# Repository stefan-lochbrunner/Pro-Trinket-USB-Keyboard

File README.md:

Pro-Trinket-USB-Keyboard
========================
A small device for programmable keyboard shortcuts.
For more infos please see [**HaD.io project page**](https://hackaday.io/project/3502-pro-trinket-usb-keyboard)

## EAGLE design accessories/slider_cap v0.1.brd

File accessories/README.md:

Accessories for the Pro Trinket Keyboard v4.2 and up

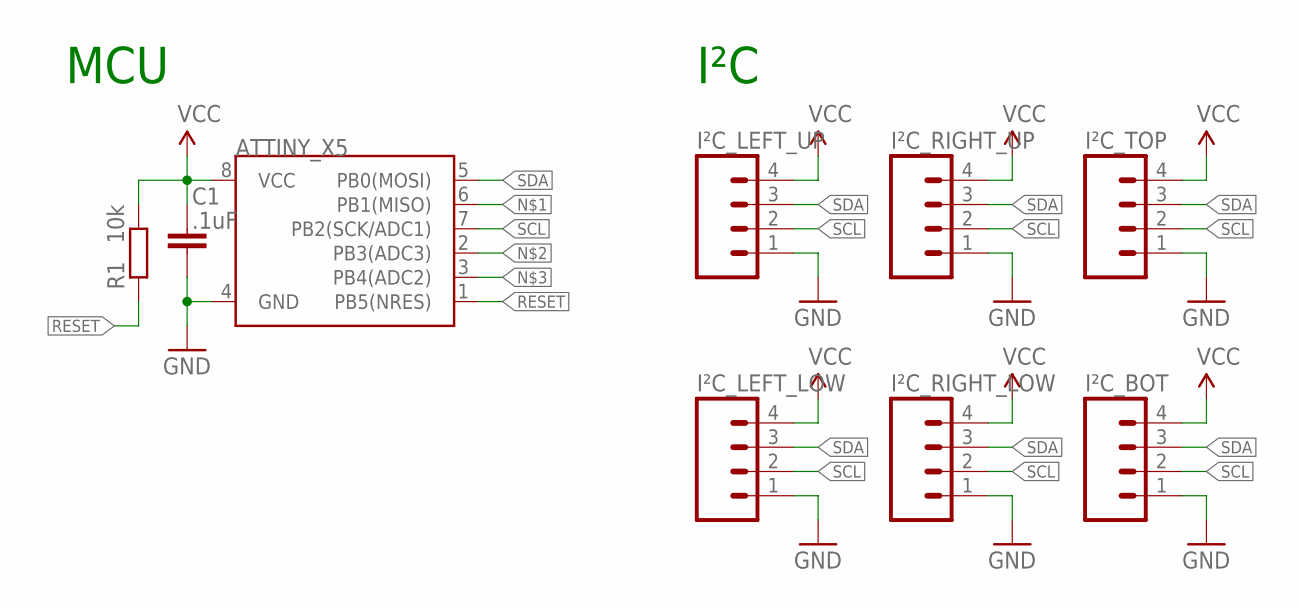
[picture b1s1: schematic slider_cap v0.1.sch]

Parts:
ATTINY_X5: ATTINY45TINY45-20-SMT; SO08-EIAJ
C1: .1uF; C805
I²C_BOT: M04PTH; 1X04
I²C_LEFT_LOW: M04PTH; 1X04
I²C_LEFT_UP: M04PTH; 1X04
I²C_RIGHT_LOW: M04PTH; 1X04
I²C_RIGHT_UP: M04PTH; 1X04
I²C_TOP: M04PTH; 1X04
R1: 10k; R805

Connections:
GND: ATTINY_X5.4 (GND), C1.2, I²C_BOT.1, I²C_LEFT_LOW.1, I²C_LEFT_UP.1, I²C_RIGHT_LOW.1, I²C_RIGHT_UP.1, I²C_TOP.1
RESET: ATTINY_X5.1 (PB5(NRES)), R1.1
SCL: ATTINY_X5.7 (PB2(SCK/ADC1)), I²C_BOT.2, I²C_LEFT_LOW.2, I²C_LEFT_UP.2, I²C_RIGHT_LOW.2, I²C_RIGHT_UP.2, I²C_TOP.2
SDA: ATTINY_X5.5 (PB0(MOSI)), I²C_BOT.3, I²C_LEFT_LOW.3, I²C_LEFT_UP.3, I²C_RIGHT_LOW.3, I²C_RIGHT_UP.3, I²C_TOP.3
VCC: ATTINY_X5.8 (VCC), C1.1, I²C_BOT.4, I²C_LEFT_LOW.4, I²C_LEFT_UP.4, I²C_RIGHT_LOW.4, I²C_RIGHT_UP.4, I²C_TOP.4, R1.2

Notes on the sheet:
I²C
MCU

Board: 2 copper layers, 9 parts (3 on the bottom side), 5 nets, no tracks yet.

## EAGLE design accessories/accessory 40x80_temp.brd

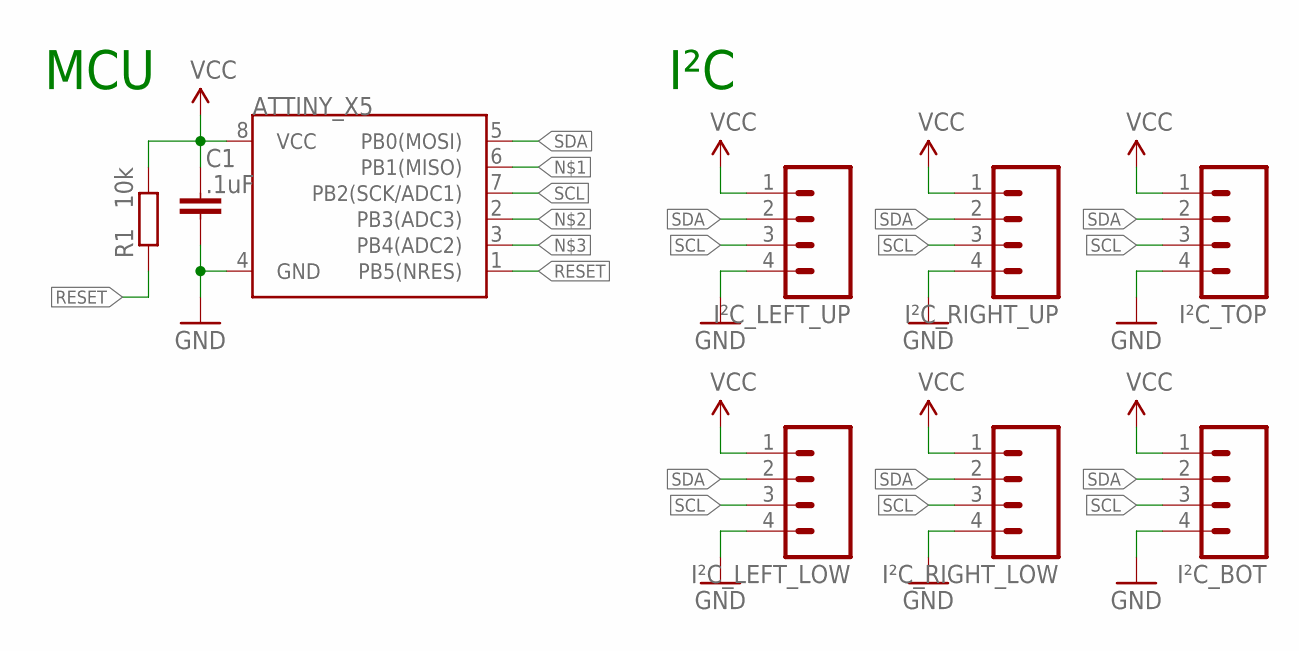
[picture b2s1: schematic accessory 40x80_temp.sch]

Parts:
ATTINY_X5: ATTINY45TINY45-20-SMT; SO08-EIAJ
C1: .1uF; C805
I²C_BOT: M04PTH; 1X04
I²C_LEFT_LOW: M04PTH; 1X04
I²C_LEFT_UP: M04PTH; 1X04
I²C_RIGHT_LOW: M04PTH; 1X04
I²C_RIGHT_UP: M04PTH; 1X04
I²C_TOP: M04PTH; 1X04
R1: 10k; R805

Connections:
GND: ATTINY_X5.4 (GND), C1.2, I²C_BOT.4, I²C_LEFT_LOW.4, I²C_LEFT_UP.4, I²C_RIGHT_LOW.4, I²C_RIGHT_UP.4, I²C_TOP.4
RESET: ATTINY_X5.1 (PB5(NRES)), R1.1
SCL: ATTINY_X5.7 (PB2(SCK/ADC1)), I²C_BOT.3, I²C_LEFT_LOW.3, I²C_LEFT_UP.3, I²C_RIGHT_LOW.3, I²C_RIGHT_UP.3, I²C_TOP.3
SDA: ATTINY_X5.5 (PB0(MOSI)), I²C_BOT.2, I²C_LEFT_LOW.2, I²C_LEFT_UP.2, I²C_RIGHT_LOW.2, I²C_RIGHT_UP.2, I²C_TOP.2
VCC: ATTINY_X5.8 (VCC), C1.1, I²C_BOT.1, I²C_LEFT_LOW.1, I²C_LEFT_UP.1, I²C_RIGHT_LOW.1, I²C_RIGHT_UP.1, I²C_TOP.1, R1.2

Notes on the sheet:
I²C
MCU

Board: 2 copper layers, 9 parts (3 on the bottom side), 5 nets, no tracks yet.

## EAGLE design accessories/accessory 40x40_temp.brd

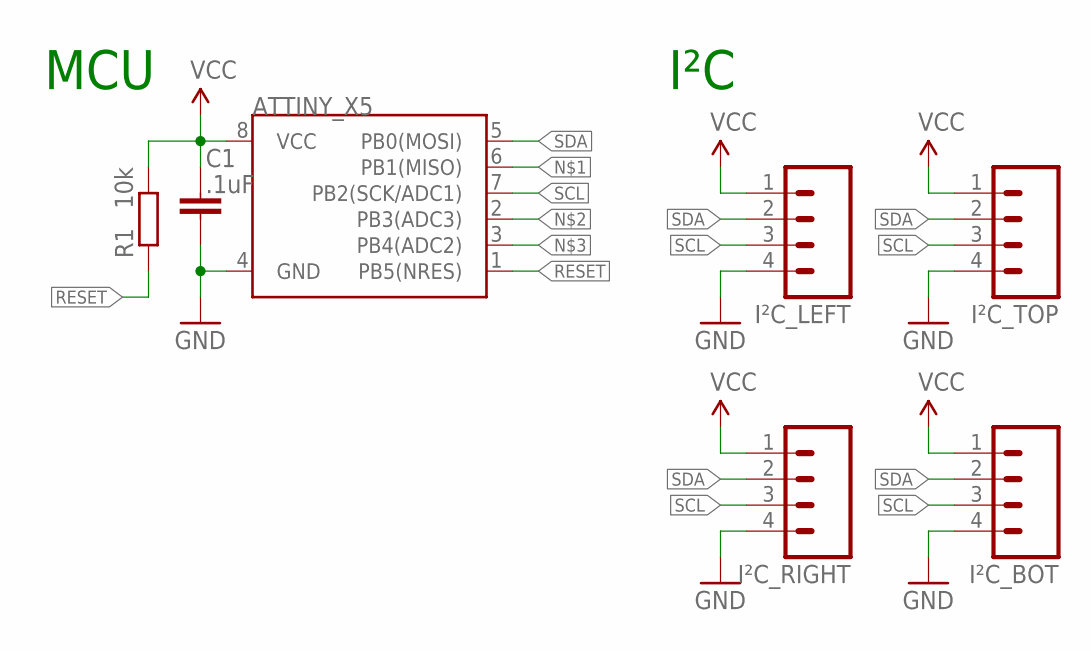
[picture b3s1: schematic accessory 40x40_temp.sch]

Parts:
ATTINY_X5: ATTINY45TINY45-20-SMT; SO08-EIAJ
C1: .1uF; C805
I²C_BOT: M04PTH; 1X04
I²C_LEFT: M04PTH; 1X04
I²C_RIGHT: M04PTH; 1X04
I²C_TOP: M04PTH; 1X04
R1: 10k; R805

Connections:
GND: ATTINY_X5.4 (GND), C1.2, I²C_BOT.4, I²C_LEFT.4, I²C_RIGHT.4, I²C_TOP.4
RESET: ATTINY_X5.1 (PB5(NRES)), R1.1
SCL: ATTINY_X5.7 (PB2(SCK/ADC1)), I²C_BOT.3, I²C_LEFT.3, I²C_RIGHT.3, I²C_TOP.3
SDA: ATTINY_X5.5 (PB0(MOSI)), I²C_BOT.2, I²C_LEFT.2, I²C_RIGHT.2, I²C_TOP.2
VCC: ATTINY_X5.8 (VCC), C1.1, I²C_BOT.1, I²C_LEFT.1, I²C_RIGHT.1, I²C_TOP.1, R1.2

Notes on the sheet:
I²C
MCU

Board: 2 copper layers, 7 parts (3 on the bottom side), 5 nets, no tracks yet.

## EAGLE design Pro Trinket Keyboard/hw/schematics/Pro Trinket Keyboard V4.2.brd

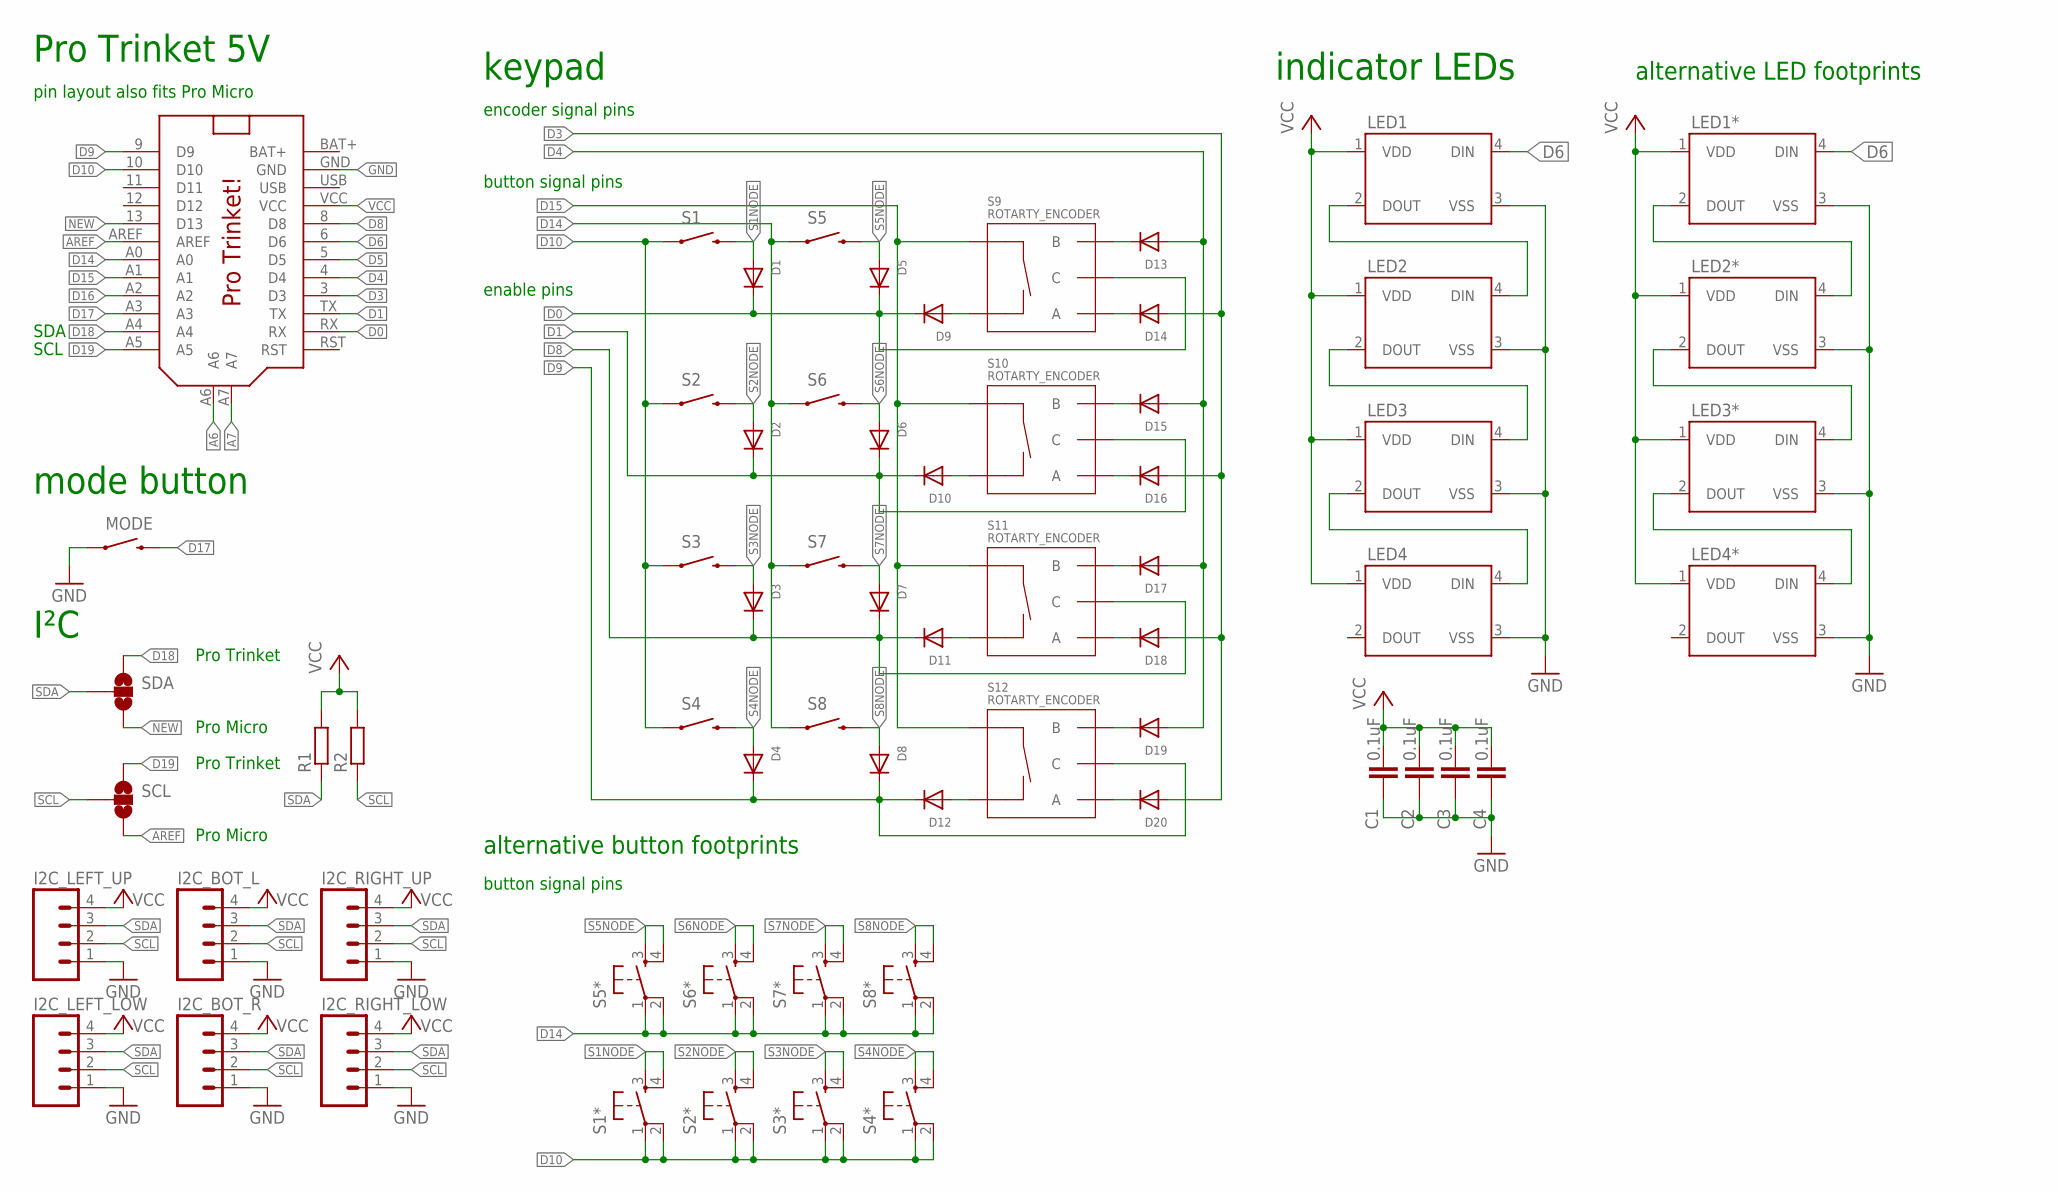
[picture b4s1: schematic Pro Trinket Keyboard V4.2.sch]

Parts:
C1, C2, C3, C4: 0.1uF; 0603-CAP
D1, D2, D3, D4, D5, D6, D7, D8, D9, D10, D11, D12, D13, D14, D15, D16, D17, D18, D19, D20: DIODESOD-123; SOD-123
I2C_BOT_L, I2C_BOT_R, I2C_LEFT_LOW, I2C_LEFT_UP, I2C_RIGHT_LOW, I2C_RIGHT_UP: M04PTH; 1X04
LED1, LED1*, LED2, LED2*, LED3, LED3*, LED4, LED4*: WS2812B
MODE: SWITCH-MOMENTARY-2SIDE_EZ; TACTILE-PTH-SIDEEZ
PRO_TRINKET: PRO_TRINKET; PROTRINKET
R1, R2: RESISTORR805-0805; R805
S1, S2, S3, S4, S5, S6, S7, S8: SWITCH-MOMENTARY-212MM; TACTILE-PTH-12MM
S1*, S2*, S3*, S4*, S5*, S6*, S7*, S8*: TACTILE-SWITCH-PTH; TAC-SWITCH-PTH
S9, S10, S11, S12: ROTARTY_ENCODER; ROTARY_ENC_PLAIN
SCL: SOLDERJUMPER_2WAYS; SJ_3
SDA: SOLDERJUMPER_2WAYS; SJ_3

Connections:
A6: PRO_TRINKET.A6
A7: PRO_TRINKET.A7
AREF: PRO_TRINKET.AREF, SCL.3
BAT+: PRO_TRINKET.BAT+
D0: D1.C, D5.C, D9.C, PRO_TRINKET.RX, S9.C
D1: D2.C, D6.C, D10.C, PRO_TRINKET.TX, S10.C
D3: D14.A, D16.A, D18.A, D20.A, PRO_TRINKET.3 (D3)
D4: D13.A, D15.A, D17.A, D19.A, PRO_TRINKET.4 (D4)
D5: PRO_TRINKET.5 (D5)
D6: LED1.4 (DIN), LED1*.4 (DIN), PRO_TRINKET.6 (D6)
D8: D3.C, D7.C, D11.C, PRO_TRINKET.8 (D8), S11.C
D9: D4.C, D8.C, D12.C, PRO_TRINKET.9 (D9), S12.C
D10: PRO_TRINKET.10 (D10), S1.1, S1.2 (1), S1*.1, S1*.2, S2.1, S2.2 (1), S2*.1, S2*.2, S3.1, S3.2 (1), S3*.1, S3*.2, S4.1, S4.2 (1), S4*.1, S4*.2
D14: PRO_TRINKET.A0, S5.1, S5.2 (1), S5*.1, S5*.2, S6.1, S6.2 (1), S6*.1, S6*.2, S7.1, S7.2 (1), S7*.1, S7*.2, S8.1, S8.2 (1), S8*.1, S8*.2
D15: PRO_TRINKET.A1, S9.SW+, S10.SW+, S11.SW+, S12.SW+
D16: PRO_TRINKET.A2
D17: MODE.2, PRO_TRINKET.A3
D18: PRO_TRINKET.A4, SDA.1
D19: PRO_TRINKET.A5, SCL.1
GND: C1.1, C2.1, C3.1, C4.1, I2C_BOT_L.1, I2C_BOT_R.1, I2C_LEFT_LOW.1, I2C_LEFT_UP.1, I2C_RIGHT_LOW.1, I2C_RIGHT_UP.1, LED1.3 (VSS), LED1*.3 (VSS), LED2.3 (VSS), LED2*.3 (VSS), LED3.3 (VSS), LED3*.3 (VSS), LED4.3 (VSS), LED4*.3 (VSS), MODE.1, PRO_TRINKET.GND
L1NODE: LED1.2 (DOUT), LED1*.2 (DOUT), LED2.4 (DIN), LED2*.4 (DIN)
L2NODE: LED2.2 (DOUT), LED2*.2 (DOUT), LED3.4 (DIN), LED3*.4 (DIN)
L3NODE: LED3.2 (DOUT), LED3*.2 (DOUT), LED4.4 (DIN), LED4*.4 (DIN)
unnamed: D10.A, S10.SW-
unnamed: D9.A, S9.SW-
unnamed: D11.A, S11.SW-
unnamed: D20.C, S12.A
unnamed: D19.C, S12.B
unnamed: D18.C, S11.A
unnamed: D12.A, S12.SW-
unnamed: D16.C, S10.A
unnamed: D15.C, S10.B
unnamed: D14.C, S9.A
unnamed: D13.C, S9.B
unnamed: D17.C, S11.B
NEW: PRO_TRINKET.13 (D13), SDA.3
S1NODE: D1.A, S1.3 (2), S1.4 (2), S1*.3, S1*.4
S2NODE: D2.A, S2.3 (2), S2.4 (2), S2*.3, S2*.4
S3NODE: D3.A, S3.3 (2), S3.4 (2), S3*.3, S3*.4
S4NODE: D4.A, S4.3 (2), S4.4 (2), S4*.3, S4*.4
S5NODE: D5.A, S5.3 (2), S5.4 (2), S5*.3, S5*.4
S6NODE: D6.A, S6.3 (2), S6.4 (2), S6*.3, S6*.4
S7NODE: D7.A, S7.3 (2), S7.4 (2), S7*.3, S7*.4
S8NODE: D8.A, S8.3 (2), S8.4 (2), S8*.3, S8*.4
SCL: I2C_BOT_L.2, I2C_BOT_R.2, I2C_LEFT_LOW.2, I2C_LEFT_UP.2, I2C_RIGHT_LOW.2, I2C_RIGHT_UP.2, R2.1, SCL.2
SDA: I2C_BOT_L.3, I2C_BOT_R.3, I2C_LEFT_LOW.3, I2C_LEFT_UP.3, I2C_RIGHT_LOW.3, I2C_RIGHT_UP.3, R1.1, SDA.2
USB: PRO_TRINKET.USB
VCC: C1.2, C2.2, C3.2, C4.2, I2C_BOT_L.4, I2C_BOT_R.4, I2C_LEFT_LOW.4, I2C_LEFT_UP.4, I2C_RIGHT_LOW.4, I2C_RIGHT_UP.4, LED1.1 (VDD), LED1*.1 (VDD), LED2.1 (VDD), LED2*.1 (VDD), LED3.1 (VDD), LED3*.1 (VDD), LED4.1 (VDD), LED4*.1 (VDD), PRO_TRINKET.VCC, R1.2, R2.2

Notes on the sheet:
keypad
mode button
indicator LEDs
Pro Trinket 5V
enable pins
encoder signal pins
button signal pins
alternative button footprints
alternative LED footprints
pin layout also fits Pro Micro
I²C
SDA
SCL
Pro Trinket
Pro Micro

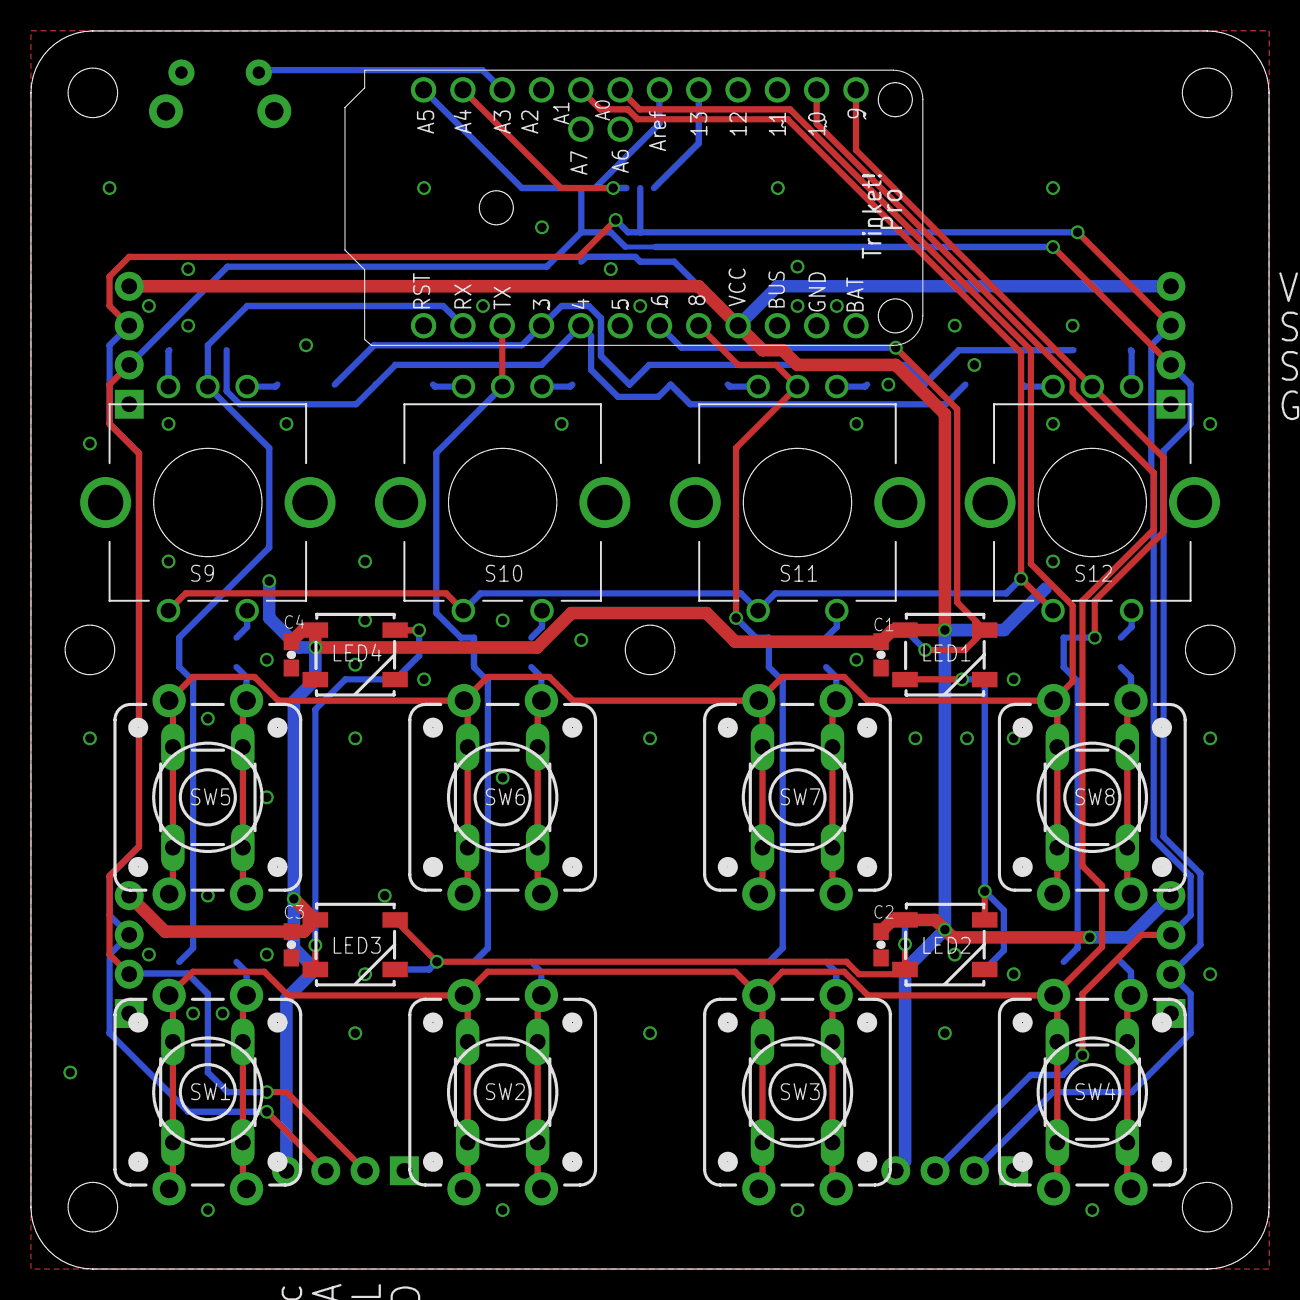
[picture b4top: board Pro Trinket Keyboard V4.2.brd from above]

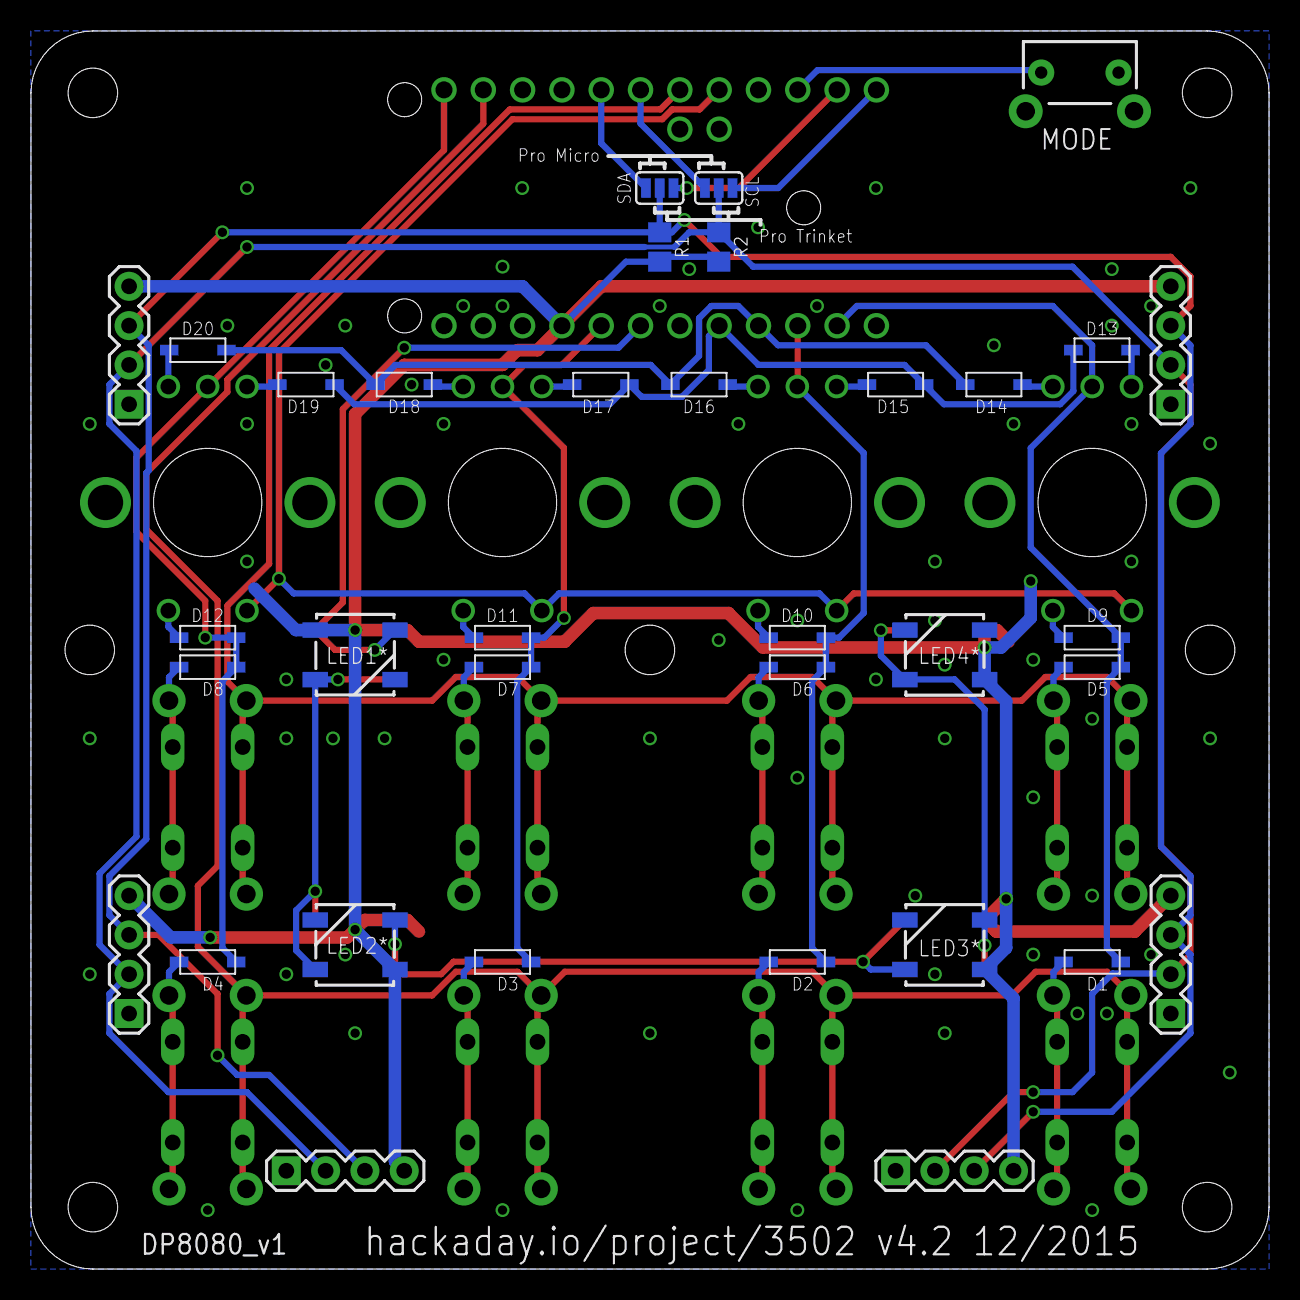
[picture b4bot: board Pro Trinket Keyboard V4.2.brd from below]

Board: 2 copper layers, 80.0 x 80.0 mm, 65 parts (35 on the bottom side), 42 nets.

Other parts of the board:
U$1: DP8080_V1

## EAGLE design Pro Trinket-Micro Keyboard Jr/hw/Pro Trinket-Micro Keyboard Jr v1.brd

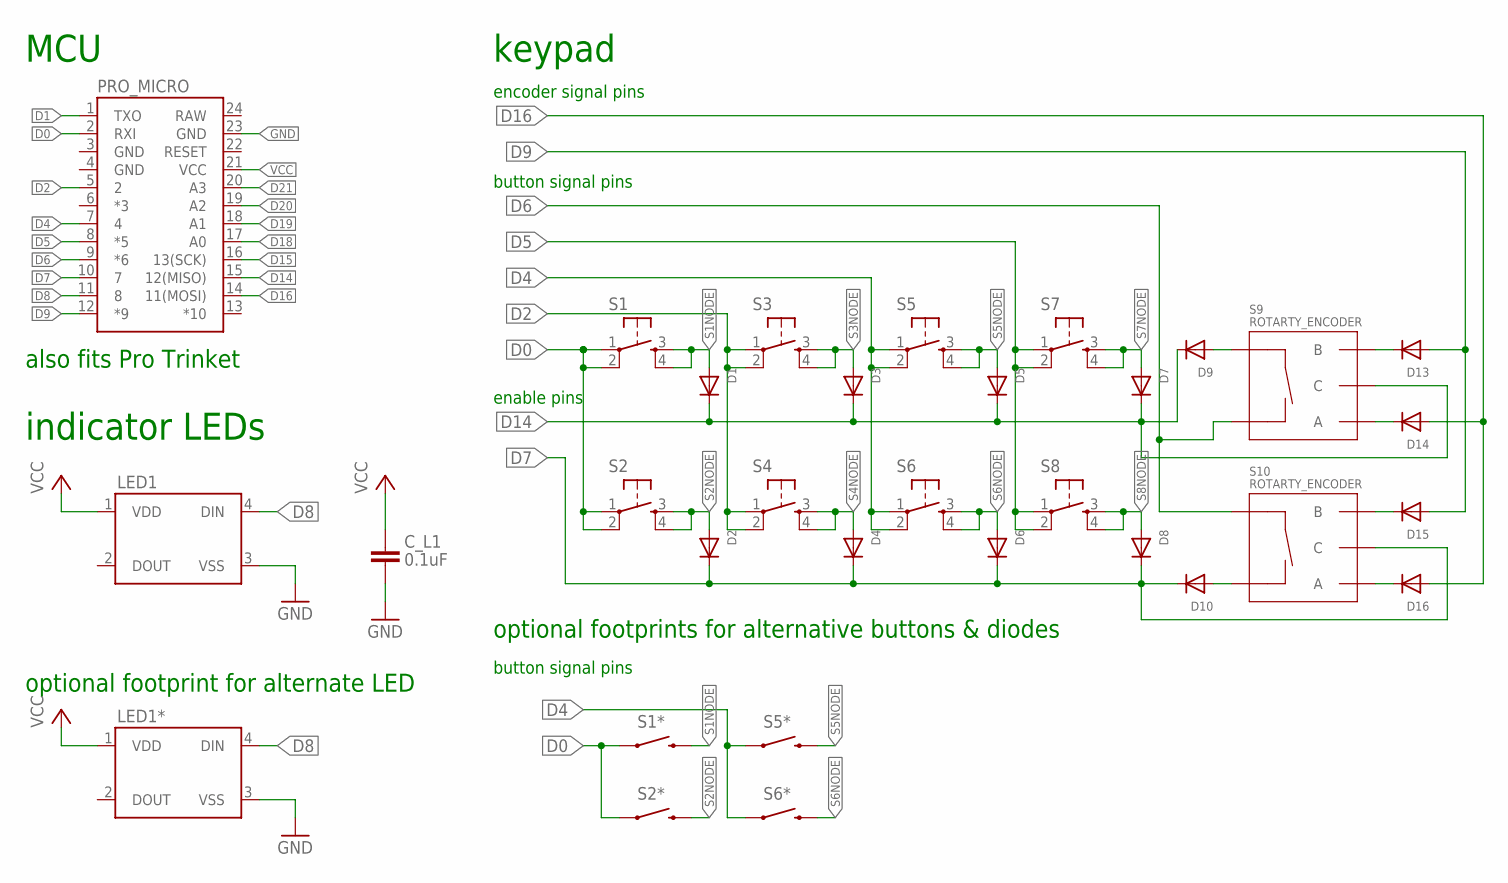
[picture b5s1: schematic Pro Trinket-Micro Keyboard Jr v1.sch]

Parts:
C_L1: 0.1uF; 0603-CAP
D1, D2, D3, D4, D5, D6, D7, D8, D9, D10, D13, D14, D15, D16: DIODESOD-123; SOD-123
LED1, LED1*: WS2812B
PRO_MICRO: ARDUINO_PRO_MICRO
S1, S2, S3, S4, S5, S6, S7, S8: TACTILE-SWITCH-PTH; TAC-SWITCH-PTH
S1*, S2*, S5*, S6*: SWITCH-MOMENTARY-212MM; TACTILE-PTH-12MM
S9, S10: ROTARTY_ENCODER; ROTARY_ENC_PLAIN

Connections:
D0: PRO_MICRO.2 (RXI), S1.1, S1.2, S1*.1, S1*.2 (1), S2.1, S2.2, S2*.1, S2*.2 (1)
D1: PRO_MICRO.1 (TXO)
D2: PRO_MICRO.5 (2), S3.1, S3.2, S4.1, S4.2
D4: PRO_MICRO.7 (4), S5.1, S5.2, S5*.1, S5*.2 (1), S6.1, S6.2, S6*.1, S6*.2 (1)
D5: PRO_MICRO.8 (*5), S7.1, S7.2, S8.1, S8.2
D6: PRO_MICRO.9 (*6), S9.SW-, S10.SW+
D7: D2.C, D4.C, D6.C, D8.C, D10.C, PRO_MICRO.10 (7), S10.C
D8: LED1.4 (DIN), LED1*.4 (DIN), PRO_MICRO.11 (8)
D9: D13.A, D15.A, PRO_MICRO.12 (*9)
D14: D1.C, D3.C, D5.C, D7.C, D9.C, PRO_MICRO.15 (12(MISO)), S9.C
D15: PRO_MICRO.16 (13(SCK))
D16: D14.A, D16.A, PRO_MICRO.14 (11(MOSI))
D18: PRO_MICRO.17 (A0)
D19: PRO_MICRO.18 (A1)
D20: PRO_MICRO.19 (A2)
D21: PRO_MICRO.20 (A3)
GND: C_L1.1, LED1.3 (VSS), LED1*.3 (VSS), PRO_MICRO.23 (GND)
unnamed: D9.A, S9.SW+
unnamed: D10.A, S10.SW-
unnamed: D16.C, S10.A
unnamed: D15.C, S10.B
unnamed: D14.C, S9.A
unnamed: D13.C, S9.B
S1NODE: D1.A, S1.3, S1.4, S1*.3 (2), S1*.4 (2)
S2NODE: D2.A, S2.3, S2.4, S2*.3 (2), S2*.4 (2)
S3NODE: D3.A, S3.3, S3.4
S4NODE: D4.A, S4.3, S4.4
S5NODE: D5.A, S5.3, S5.4, S5*.3 (2), S5*.4 (2)
S6NODE: D6.A, S6.3, S6.4, S6*.3 (2), S6*.4 (2)
S7NODE: D7.A, S7.3, S7.4
S8NODE: D8.A, S8.3, S8.4
VCC: C_L1.2, LED1.1 (VDD), LED1*.1 (VDD), PRO_MICRO.21 (VCC)

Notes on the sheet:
keypad
indicator LEDs
enable pins
encoder signal pins
button signal pins
optional footprints for alternative buttons & diodes
optional footprint for alternate LED
MCU
also fits Pro Trinket

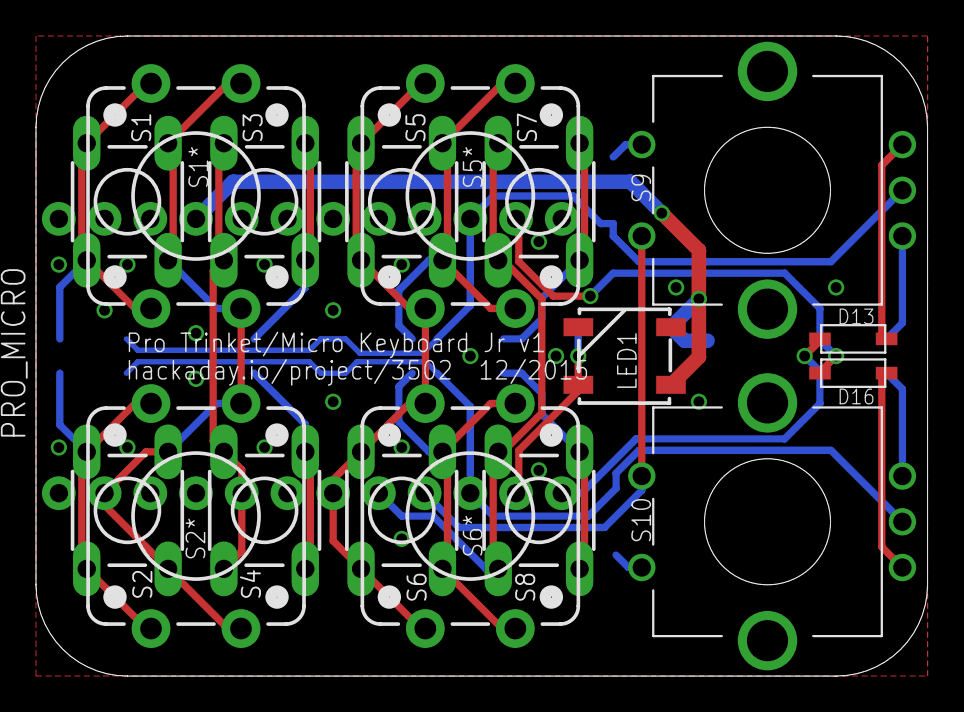
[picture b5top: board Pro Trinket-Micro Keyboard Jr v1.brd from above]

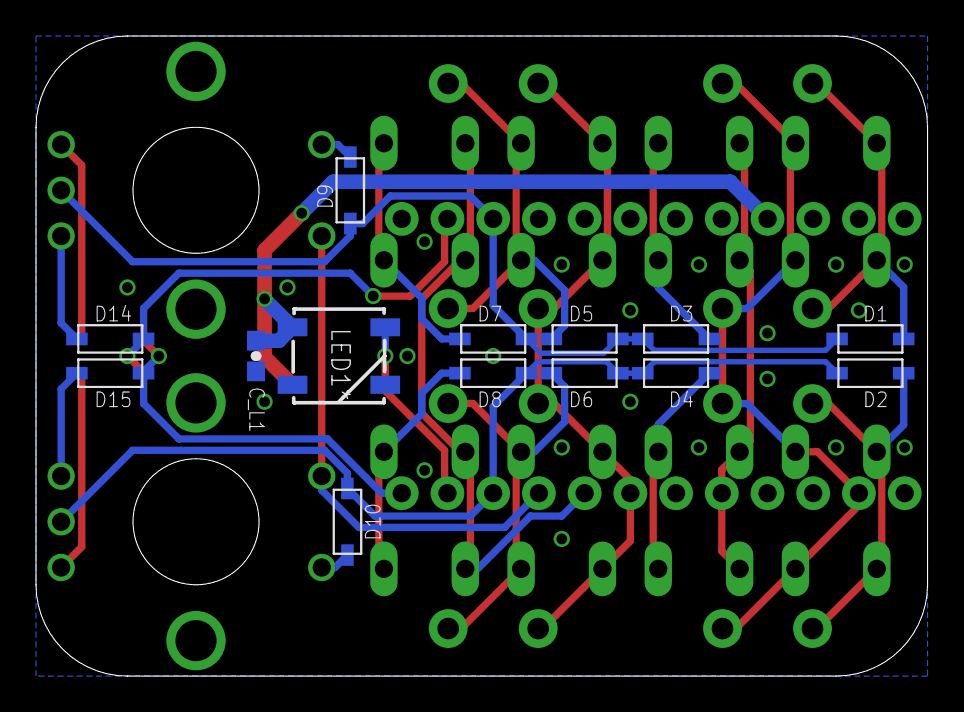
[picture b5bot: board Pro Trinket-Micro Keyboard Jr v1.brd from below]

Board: 2 copper layers, 49.5 x 35.6 mm, 32 parts (14 on the bottom side), 26 nets.

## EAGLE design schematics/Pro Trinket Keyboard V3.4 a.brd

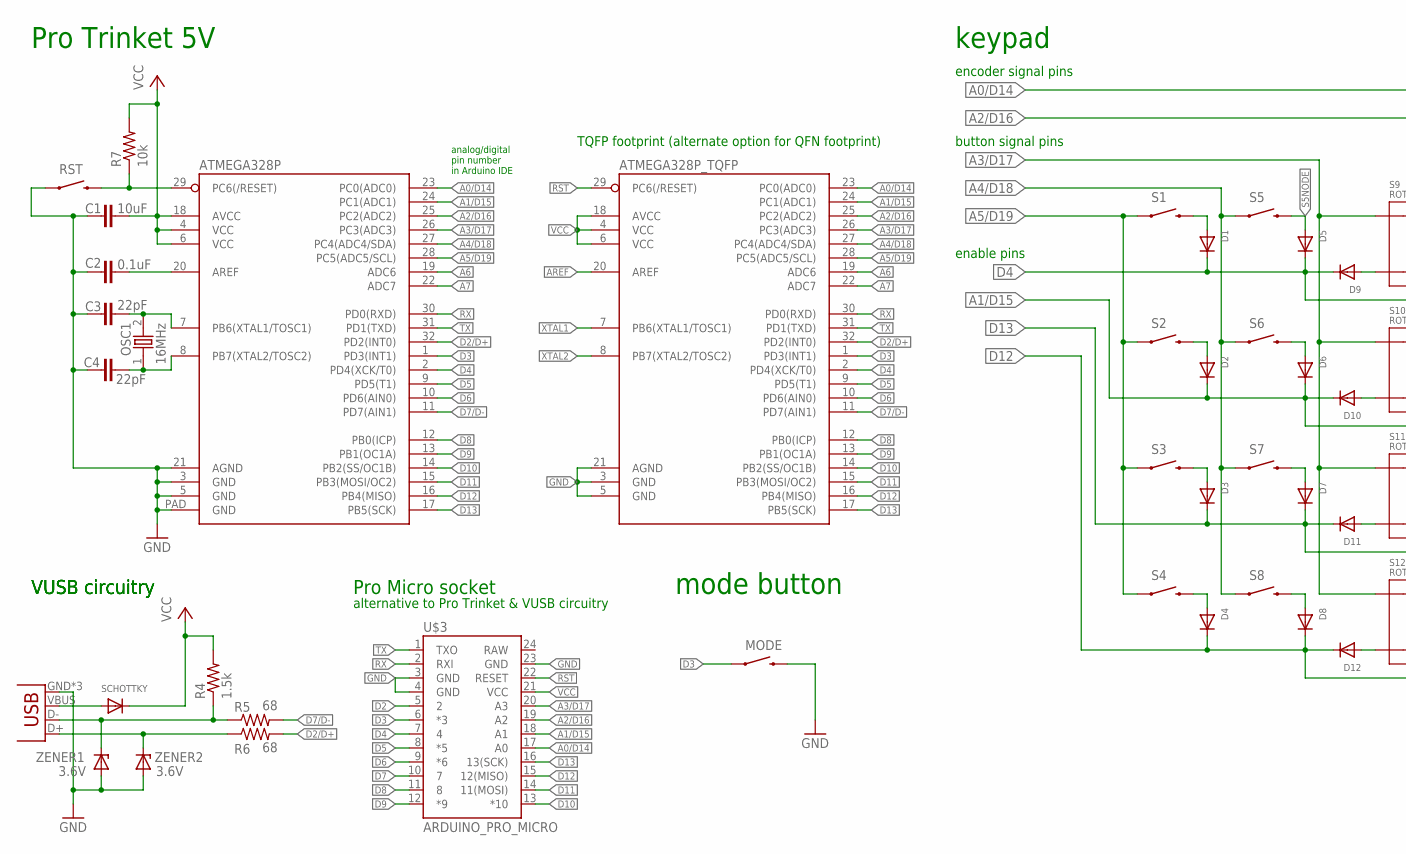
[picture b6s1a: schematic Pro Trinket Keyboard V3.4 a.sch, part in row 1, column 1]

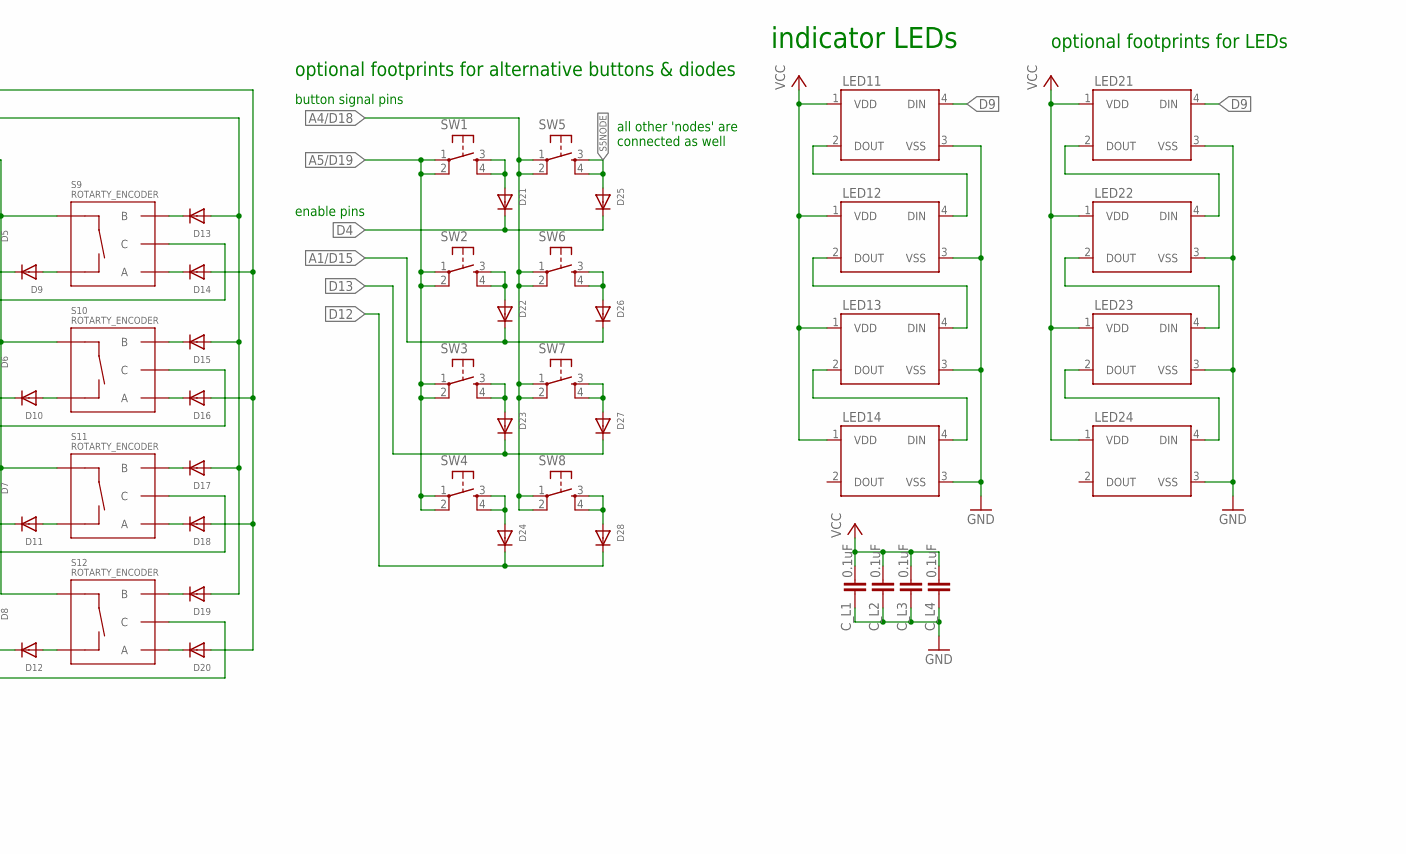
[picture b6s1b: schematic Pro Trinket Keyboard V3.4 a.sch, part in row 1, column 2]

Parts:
ATMEGA328P: ATMEGA328P_MLFMLF32; MLF32-PAD
ATMEGA328P_TQFP: ATMEGA328P_TQFP; TQFP32-08
C1: 10uF; 0603-CAP
C2: 0.1uF; 0603-CAP
C3, C4: 22pF; 0603-CAP
C_L1, C_L2, C_L3, C_L4: 0.1uF; 0603-CAP
D1, D2, D3, D4, D5, D6, D7, D8, D9, D10, D11, D12, D13, D14, D15, D16, D17, D18, D19, D20, D21, D22, D23, D24, D25, D26, D27, D28: DIODESOD-123; SOD-123
LED11, LED12, LED13, LED14, LED21, LED22, LED23, LED24: WS2812B
MODE: SWITCH-MOMENTARY-2SIDE_EZ; TACTILE-PTH-SIDEEZ
OSC1: 16MHz; HC-49U
R4: 1.5k; 0805
R5, R6: 68; 0805
R7: 10k; 0805
RST: SWITCH-MOMENTARY-2SIDE_EZ; TACTILE-PTH-SIDEEZ
S1, S2, S3, S4, S5, S6, S7, S8: SWITCH-MOMENTARY-212MM; TACTILE-PTH-12MM
S9, S10, S11, S12: ROTARTY_ENCODER; ROTARY_ENC_PLAIN
SCHOTTKY: DIODESMA; SMADIODE
SW1, SW2, SW3, SW4, SW5, SW6, SW7, SW8: TACTILE-SWITCH-PTH; TAC-SWITCH-PTH
U$3: ARDUINO_PRO_MICRO
UUSB: USB-MICROB
ZENER1, ZENER2: 3.6V; SOD80C

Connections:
A0/D14: ATMEGA328P.23 (PC0(ADC0)), ATMEGA328P_TQFP.23 (PC0(ADC0)), D14.A, D16.A, D18.A, D20.A, U$3.17 (A0)
A1/D15: ATMEGA328P.24 (PC1(ADC1)), ATMEGA328P_TQFP.24 (PC1(ADC1)), D2.C, D6.C, D10.C, D22.C, D26.C, S10.C, U$3.18 (A1)
A2/D16: ATMEGA328P.25 (PC2(ADC2)), ATMEGA328P_TQFP.25 (PC2(ADC2)), D13.A, D15.A, D17.A, D19.A, U$3.19 (A2)
A3/D17: ATMEGA328P.26 (PC3(ADC3)), ATMEGA328P_TQFP.26 (PC3(ADC3)), S9.SW+, S10.SW+, S11.SW+, S12.SW+, U$3.20 (A3)
A4/D18: ATMEGA328P.27 (PC4(ADC4/SDA)), ATMEGA328P_TQFP.27 (PC4(ADC4/SDA)), S5.1, S5.2 (1), S6.1, S6.2 (1), S7.1, S7.2 (1), S8.1, S8.2 (1), SW5.1, SW5.2, SW6.1, SW6.2, SW7.1, SW7.2, SW8.1, SW8.2
A5/D19: ATMEGA328P.28 (PC5(ADC5/SCL)), ATMEGA328P_TQFP.28 (PC5(ADC5/SCL)), S1.1, S1.2 (1), S2.1, S2.2 (1), S3.1, S3.2 (1), S4.1, S4.2 (1), SW1.1, SW1.2, SW2.1, SW2.2, SW3.1, SW3.2, SW4.1, SW4.2
A6: ATMEGA328P.19 (ADC6), ATMEGA328P_TQFP.19 (ADC6)
A7: ATMEGA328P.22 (ADC7), ATMEGA328P_TQFP.22 (ADC7)
AREF: ATMEGA328P.20 (AREF), ATMEGA328P_TQFP.20 (AREF), C2.2
D2: U$3.5 (2)
D2/D+: ATMEGA328P.32 (PD2(INT0)), ATMEGA328P_TQFP.32 (PD2(INT0)), R6.2
D3: ATMEGA328P.1 (PD3(INT1)), ATMEGA328P_TQFP.1 (PD3(INT1)), MODE.1, U$3.6 (*3)
D4: ATMEGA328P.2 (PD4(XCK/T0)), ATMEGA328P_TQFP.2 (PD4(XCK/T0)), D1.C, D5.C, D9.C, D21.C, D25.C, S9.C, U$3.7 (4)
D5: ATMEGA328P.9 (PD5(T1)), ATMEGA328P_TQFP.9 (PD5(T1)), U$3.8 (*5)
D6: ATMEGA328P.10 (PD6(AIN0)), ATMEGA328P_TQFP.10 (PD6(AIN0)), U$3.9 (*6)
D7: U$3.10 (7)
D7/D-: ATMEGA328P.11 (PD7(AIN1)), ATMEGA328P_TQFP.11 (PD7(AIN1)), R5.2
D8: ATMEGA328P.12 (PB0(ICP)), ATMEGA328P_TQFP.12 (PB0(ICP)), U$3.11 (8)
D9: ATMEGA328P.13 (PB1(OC1A)), ATMEGA328P_TQFP.13 (PB1(OC1A)), LED11.4 (DIN), LED21.4 (DIN), U$3.12 (*9)
D10: ATMEGA328P.14 (PB2(SS/OC1B)), ATMEGA328P_TQFP.14 (PB2(SS/OC1B)), U$3.13 (*10)
D11: ATMEGA328P.15 (PB3(MOSI/OC2)), ATMEGA328P_TQFP.15 (PB3(MOSI/OC2)), U$3.14 (11(MOSI))
D12: ATMEGA328P.16 (PB4(MISO)), ATMEGA328P_TQFP.16 (PB4(MISO)), D4.C, D8.C, D12.C, D24.C, D28.C, S12.C, U$3.15 (12(MISO))
D13: ATMEGA328P.17 (PB5(SCK)), ATMEGA328P_TQFP.17 (PB5(SCK)), D3.C, D7.C, D11.C, D23.C, D27.C, S11.C, U$3.16 (13(SCK))
GND: ATMEGA328P.3 (GND), ATMEGA328P.5 (GND), ATMEGA328P.21 (AGND), ATMEGA328P.PAD (GND), ATMEGA328P_TQFP.3 (GND), ATMEGA328P_TQFP.5 (GND), ATMEGA328P_TQFP.21 (AGND), C1.1, C2.1, C3.1, C4.2, C_L1.1, C_L2.1, C_L3.1, C_L4.1, LED11.3 (VSS), LED12.3 (VSS), LED13.3 (VSS), LED14.3 (VSS), LED21.3 (VSS), LED22.3 (VSS), LED23.3 (VSS), LED24.3 (VSS), MODE.2, RST.1, U$3.3 (GND), U$3.4 (GND), U$3.23 (GND), UUSB.GND, UUSB.MT1 (GND), UUSB.MT2 (GND), ZENER1.A, ZENER2.A
L1NODE: LED11.2 (DOUT), LED12.4 (DIN), LED21.2 (DOUT), LED22.4 (DIN)
L2NODE: LED12.2 (DOUT), LED13.4 (DIN), LED22.2 (DOUT), LED23.4 (DIN)
L3NODE: LED13.2 (DOUT), LED14.4 (DIN), LED23.2 (DOUT), LED24.4 (DIN)
unnamed: SCHOTTKY.A, UUSB.VBUS
unnamed: R4.1, R5.1, UUSB.D-, ZENER1.C
unnamed: R6.1, UUSB.D+, ZENER2.C
unnamed: D10.A, S10.SW-
unnamed: D9.A, S9.SW-
unnamed: D11.A, S11.SW-
unnamed: D20.C, S12.A
unnamed: D19.C, S12.B
unnamed: D18.C, S11.A
unnamed: D12.A, S12.SW-
unnamed: D16.C, S10.A
unnamed: D15.C, S10.B
unnamed: D14.C, S9.A
unnamed: D13.C, S9.B
unnamed: D17.C, S11.B
RST: ATMEGA328P.29 (PC6(/RESET)), ATMEGA328P_TQFP.29 (PC6(/RESET)), R7.1, RST.2, U$3.22 (RESET)
RX: ATMEGA328P.30 (PD0(RXD)), ATMEGA328P_TQFP.30 (PD0(RXD)), U$3.2 (RXI)
S1NODE: D1.A, D21.A, S1.3 (2), S1.4 (2), SW1.3, SW1.4
S2NODE: D2.A, D22.A, S2.3 (2), S2.4 (2), SW2.3, SW2.4
S3NODE: D3.A, D23.A, S3.3 (2), S3.4 (2), SW3.3, SW3.4
S4NODE: D4.A, D24.A, S4.3 (2), S4.4 (2), SW4.3, SW4.4
S5NODE: D5.A, D25.A, S5.3 (2), S5.4 (2), SW5.3, SW5.4
S6NODE: D6.A, D26.A, S6.3 (2), S6.4 (2), SW6.3, SW6.4
S7NODE: D7.A, D27.A, S7.3 (2), S7.4 (2), SW7.3, SW7.4
S8NODE: D8.A, D28.A, S8.3 (2), S8.4 (2), SW8.3, SW8.4
TX: ATMEGA328P.31 (PD1(TXD)), ATMEGA328P_TQFP.31 (PD1(TXD)), U$3.1 (TXO)
VCC: ATMEGA328P.4 (VCC), ATMEGA328P.6 (VCC), ATMEGA328P.18 (AVCC), ATMEGA328P_TQFP.4 (VCC), ATMEGA328P_TQFP.6 (VCC), ATMEGA328P_TQFP.18 (AVCC), C1.2, C_L1.2, C_L2.2, C_L3.2, C_L4.2, LED11.1 (VDD), LED12.1 (VDD), LED13.1 (VDD), LED14.1 (VDD), LED21.1 (VDD), LED22.1 (VDD), LED23.1 (VDD), LED24.1 (VDD), R4.2, R7.2, SCHOTTKY.C, U$3.21 (VCC)
XTAL1: ATMEGA328P.7 (PB6(XTAL1/TOSC1)), ATMEGA328P_TQFP.7 (PB6(XTAL1/TOSC1)), C3.2, OSC1.2
XTAL2: ATMEGA328P.8 (PB7(XTAL2/TOSC2)), ATMEGA328P_TQFP.8 (PB7(XTAL2/TOSC2)), C4.1, OSC1.1

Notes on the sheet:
keypad
mode button
indicator LEDs
Pro Trinket 5V
analog/digital pin number in Arduino IDE
VUSB circuitry
Pro Micro socket
enable pins
encoder signal pins
button signal pins
TQFP footprint (alternate option for QFN footprint)
optional footprints for alternative buttons & diodes
all other 'nodes' are connected as well
alternative to Pro Trinket & VUSB circuitry
optional footprints for LEDs

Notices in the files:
parts and their libraries:
SparkFun-Electromechanical: Licensing: CC v3.0 Share-Alike You are welcome to use this library for commercial purposes.
SparkFun-Capacitors: Licensing: Creative Commons ShareAlike 4.0 International - https://creativecommons.org/licenses/by-sa/4.0
